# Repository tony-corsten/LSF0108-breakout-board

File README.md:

# LSF0108-breakout-board
# Overview
The LSF0108 is a octal level translator that can operate on very fast signals (nominally, 60 - 100MHz), and includes auto-detection of the signal direction for translation. Typical level translators operate slowly and have unreasonable settling times for fast protocols like I2C or SPI. This board has been tested for translation from 3.3V to 5V and 5V to 3.3V, and consistently outperforms boards that are typically offered with breakouts like the [TXB0104](http://www.ti.com/lit/ds/symlink/txb0104.pdf), which has a nominal rise-time of 40ns/V (only 5MHz maximum frequency!).  [You can find the official documentation for the chip used in this design here](http://www.ti.com/lit/ds/symlink/lsf0102.pdf). This is a breakout board made in Kicad with 2.54mm through holes for input and output voltages (your choice of header pins or a screw terminal block!). Note that in this design, the Output Enable and the +High V are tied together, to make designing easier. If you want to have the OE to be controllable, you will need to make changes to the schematic and put appropriate pullup resistors (see the technical document). 

# Navigating this repo
The main folder contains relevant Kicad files (.pro, .pcb, .sch). The `gerber` directory has a PCB-fabrication ready set of gerber files. 

# Board images
PCB Layout:

Schematic:

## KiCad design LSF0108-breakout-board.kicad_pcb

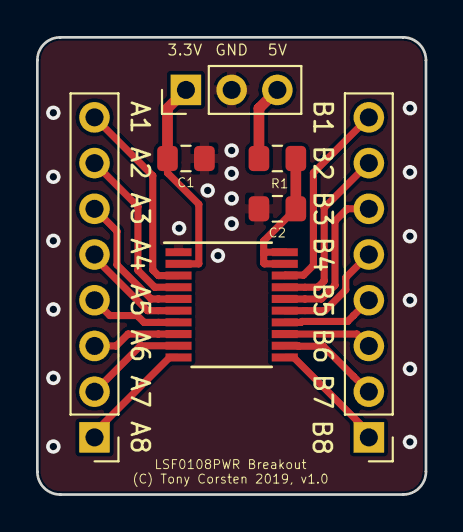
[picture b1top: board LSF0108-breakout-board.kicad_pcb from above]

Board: 2 copper layers, 21.6 x 25.4 mm, 7 parts (0 on the bottom side), 20 nets.

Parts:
C1, C2: 0.1uF; C_0805_2012Metric_Pad1.15x1.40mm_HandSolder
J1, J2: Conn_01x08; PinHeader_1x08_P2.54mm_Vertical
J3: Conn_01x03; PinHeader_1x03_P2.54mm_Vertical
R1: 200kOhm; R_0805_2012Metric_Pad1.15x1.40mm_HandSolder
U1: LSF0108PWR; TSSOP-20_4.4x6.5mm_P0.65mm

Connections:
GND: C1.2, C2.1, J3.2, U1.1
unnamed: C1.1, J3.1, U1.2
unnamed: C2.2, R1.1, U1.19, U1.20
unnamed: J1.1, U1.10
unnamed: J1.2, U1.9
unnamed: J1.3, U1.8
unnamed: J1.4, U1.7
unnamed: J1.5, U1.6
unnamed: J1.6, U1.5
unnamed: J1.7, U1.4
unnamed: J1.8, U1.3
unnamed: J2.1, U1.11
unnamed: J2.2, U1.12
unnamed: J2.3, U1.13
unnamed: J2.4, U1.14
unnamed: J2.5, U1.15
unnamed: J2.6, U1.16
unnamed: J2.7, U1.17
unnamed: J2.8, U1.18
unnamed: J3.3, R1.2
